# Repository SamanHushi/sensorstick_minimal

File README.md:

# minimal-co2-pcb

> [!NOTE]
> This board has not been physically tested.

## Todo

- [ ] Integrate into case

## Build of Materials (BOM)

Interactive BOM: https://samanhushi.github.io/sensorstick_minimal/

- 1x [ESP32-C3 SuperMini](https://www.aliexpress.com/item/1005006599448997.html)
- 1x [USB A plug](https://www.lcsc.com/product-detail/usb-connectors_xkb-connection-u217-041n-4bv81_C319178.html/?href=jlc-SMT%2F%3Fhref%3Djlc-SMT)
- 1x [SCD40 CO2 sensor](https://de.aliexpress.com/item/1005002905505683.html)
- 1x [SGP40](https://www.mouser.de/ProductDetail/Sensirion/SGP40-D-R4?qs=yqaQSyyJnNgaRqiZfsbS1Q%3D%3D)
- 1x [SHT40](https://www.mouser.de/ProductDetail/Sensirion/SHT40-AD1B-R2?qs=zW32dvEIR3scTT6A4VuzaQ%3D%3D)
- 1x [Ambient Light Sensor](https://www.lcsc.com/product-detail/C504893.html?s_z=n_C504893)

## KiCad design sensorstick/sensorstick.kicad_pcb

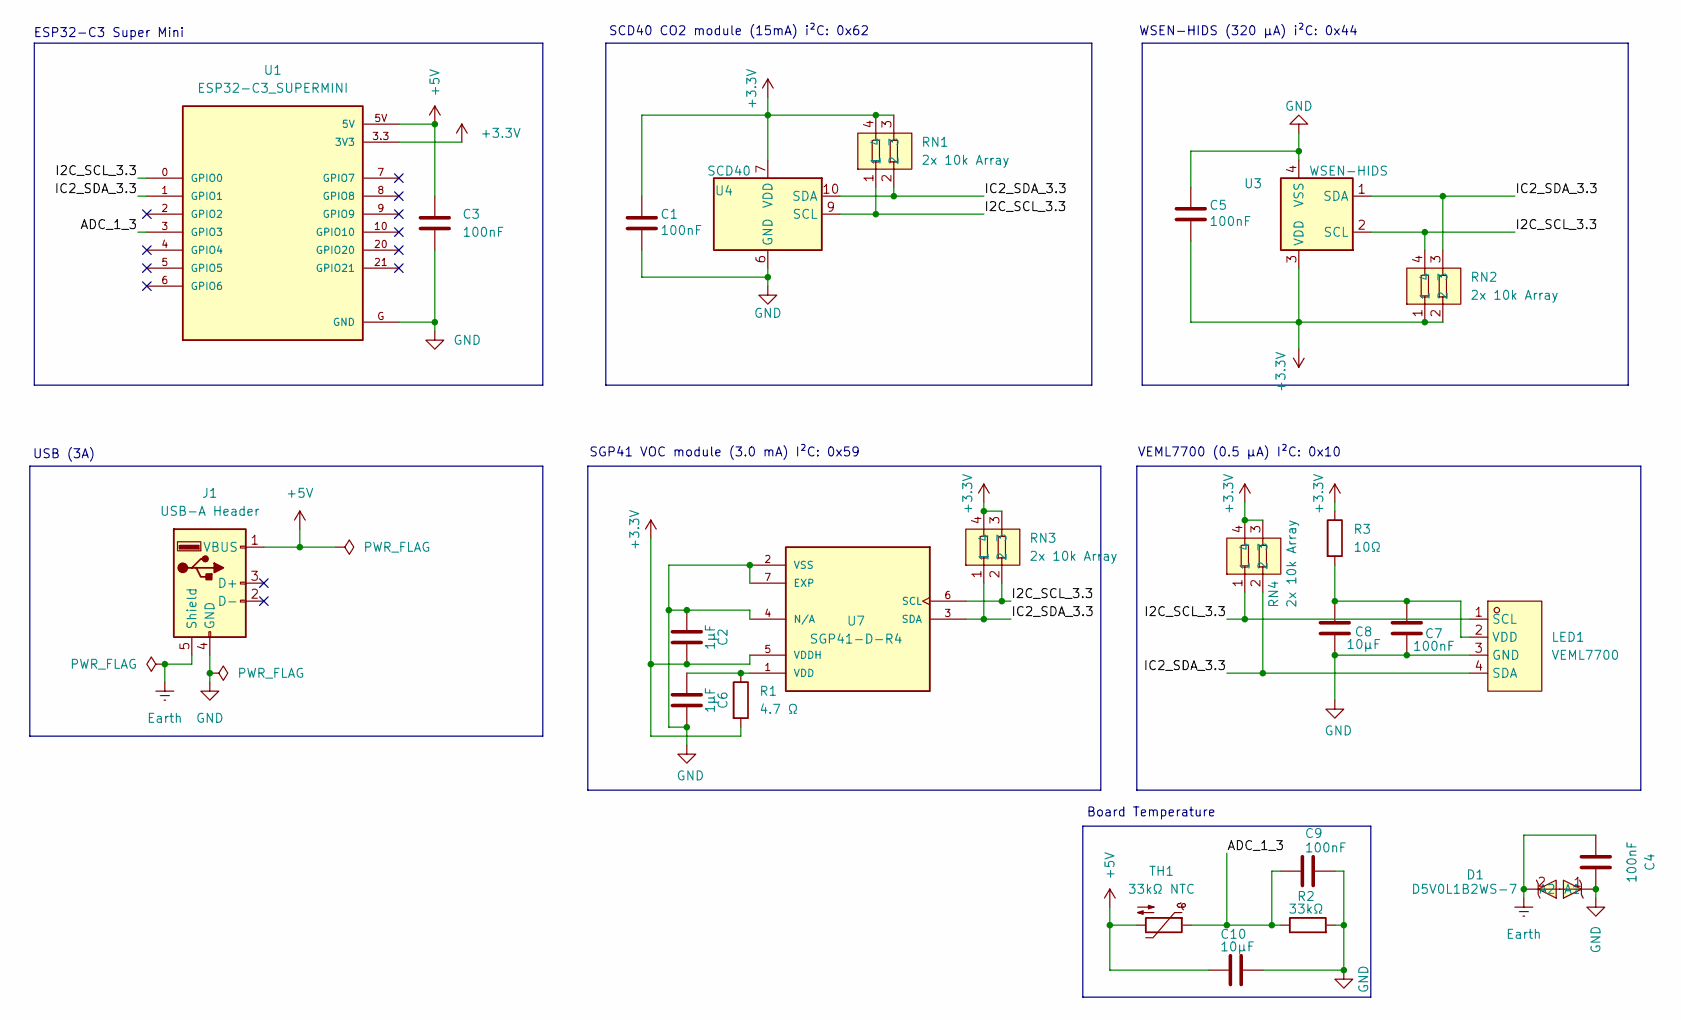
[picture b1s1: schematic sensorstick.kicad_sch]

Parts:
C1, C3, C4, C5, C7: 100nF; C_0603_1608Metric; partdb_id 573; LCSC C1591
C2, C6: 1μF; C_0603_1608Metric; partdb_id 428; LCSC C1591
C8: 10μF; C_0603_1608Metric; partdb_id 19; LCSC C1591
C9: 100nF; C_0603_1608Metric; partdb_id 573; LCSC C458914
C10: 10μF; C_0603_1608Metric; partdb_id 19; LCSC C458914
D1: D5V0L1B2WS-7; SOD-323_L1.8-W1.3-LS2.5-BI; partdb_id 429; LCSC Part C182013
J1: USB-A Header; USB-A-SMD_U217-041N-4BV81; partdb_id 248; LCSC Part C319178
LED1: VEML7700; LED-SMD_4P-L6.8-W2.4_VEML7700-TR; partdb_id 589; LCSC Part C504893
R1: 4.7 Ω; R_0603_1608Metric; partdb_id 330
R2: 33kΩ; R_0603_1608Metric; partdb_id 559
R3: 10Ω; R_0603_1608Metric; partdb_id 208
RN1, RN2, RN3, RN4: 2x 10k Array; RES-ARRAY-SMD_0402-4P-L1.0-W1.0-BL; partdb_id 431; LCSC Part C2765527
TH1: 33kΩ NTC; R_0603_1608Metric; partdb_id 571
U1: ESP32-C3_SUPERMINI; ESP32-C3_SUPERMINI_SMD; partdb_id 247
U3: WSEN-HIDS; Sensirion_DFN-4_1.5x1.5mm_P0.8mm_SHT4x_NoCentralPad; partdb_id 584
U4: SCD40; Sensirion_SCD4x-1EP_10.1x10.1mm_P1.25mm_EP4.8x4.8mm; partdb_id 566
U7: SGP41-D-R4; XDCR_SGP41-D-R4; PARTREV 1.0

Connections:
+3.3V: C1.2, C2.2, C5.1, R1.2, R3.1, RN1.3, RN1.4, RN2.1, RN2.2, RN3.3, RN3.4, RN4.3, RN4.4, U1.3.3 (3V3), U3.3 (VDD), U4.7 (VDD), U4.19 (VDD), U7.5 (VDDH)
+5V: C3.1, C10.1, J1.1 (VBUS), TH1.2, U1.5V
/ADC_1_3: C9.1, R2.1, TH1.1, U1.3 (GPIO3)
/I2C_SCL_3.3: LED1.1 (SCL), RN1.1, RN2.4, RN3.2, RN4.1, U1.0 (GPIO0), U3.2 (SCL), U4.9 (SCL), U7.6 (SCL)
/IC2_SDA_3.3: LED1.4 (SDA), RN1.2, RN2.3, RN3.1, RN4.2, U1.1 (GPIO1), U3.1 (SDA), U4.10 (SDA), U7.3 (SDA)
Earth: C4.1, D1.2 (A1), J1.5 (Shield), J1.6 (Shield)
GND: C1.1, C2.1, C3.2, C4.2, C5.2, C6.2, C7.2, C8.2, C9.2, C10.2, D1.1 (A2), J1.4 (GND), LED1.3 (GND), R2.2, U1.G (GND), U3.4 (VSS), U4.6 (GND), U4.20 (GND), U4.21 (GND), U7.2 (VSS), U7.4 (N/A), U7.7 (EXP)
unnamed: C7.1, C8.1, LED1.2 (VDD), R3.2
unnamed: C6.1, R1.1, U7.1 (VDD)

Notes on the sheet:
SCD40 CO2 module (15mA) i²C: 0x62
SGP41 VOC module (3.0 mA) I²C: 0x59
Board Temperature
ESP32-C3 Super Mini
WSEN-HIDS (320 μA) i²C: 0x44
USB (3A)
VEML7700 (0.5 μA) I²C: 0x10

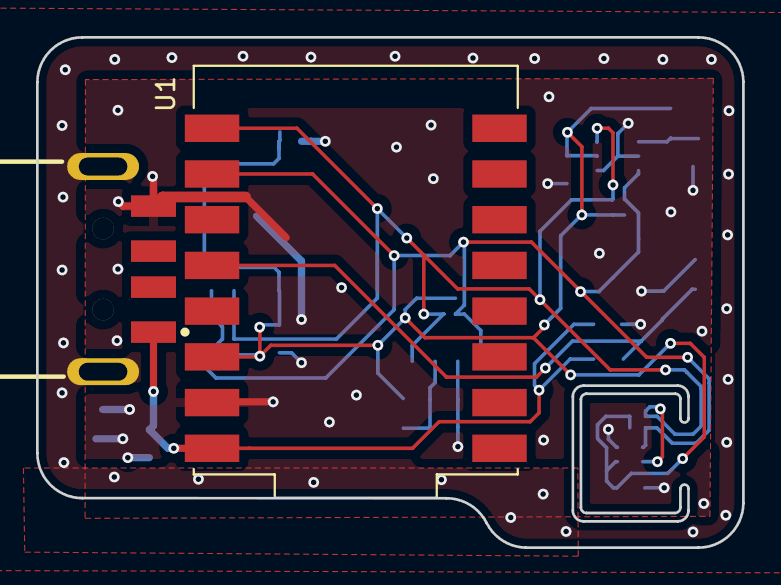
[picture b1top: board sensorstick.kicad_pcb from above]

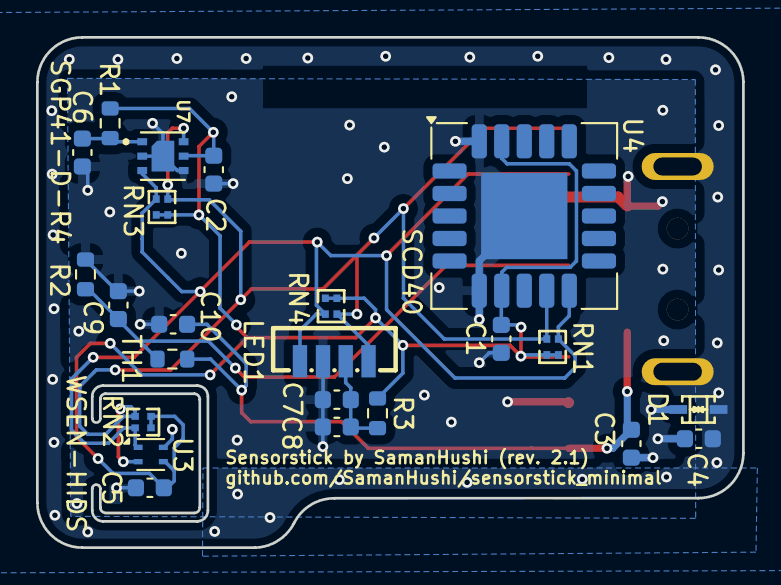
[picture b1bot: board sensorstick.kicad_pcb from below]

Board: 4 copper layers, 39.2 x 28.4 mm, 25 parts (23 on the bottom side), 9 nets.

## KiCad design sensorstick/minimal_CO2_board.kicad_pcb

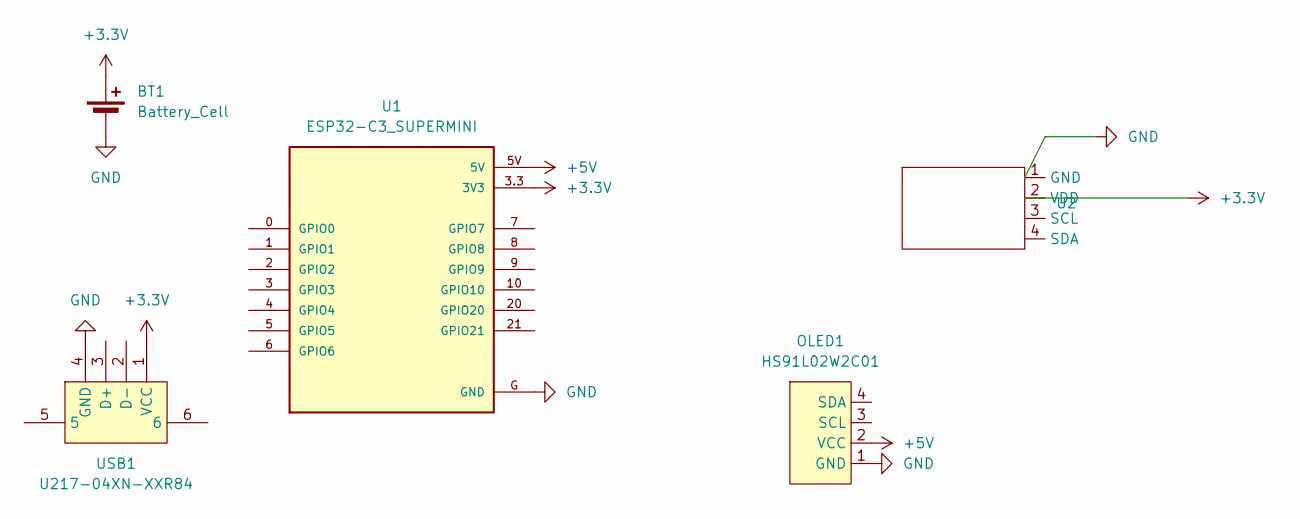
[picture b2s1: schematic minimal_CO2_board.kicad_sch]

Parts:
BT1: Battery_Cell; BatteryHolder_Keystone_1060_1x2032
OLED1: HS91L02W2C01; OLED-TH_L38.0-W12.0_HS91L02W2C01; LCSC Part C5248081
U1: ESP32-C3_SUPERMINI; ESP32-C3_SUPERMINI_SMD
U2: SCD40_CO2_module
USB1: U217-04XN-XXR84; USB-A-SMD_U217-041N-4BV81; LCSC Part C319178

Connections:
+3.3V: BT1.1 (+), U1.3.3 (3V3), U2.2 (VDD), USB1.1 (VCC)
+5V: OLED1.2 (VCC), U1.5V
GND: BT1.2 (-), OLED1.1 (GND), U1.G (GND), U2.1 (GND), USB1.4 (GND)

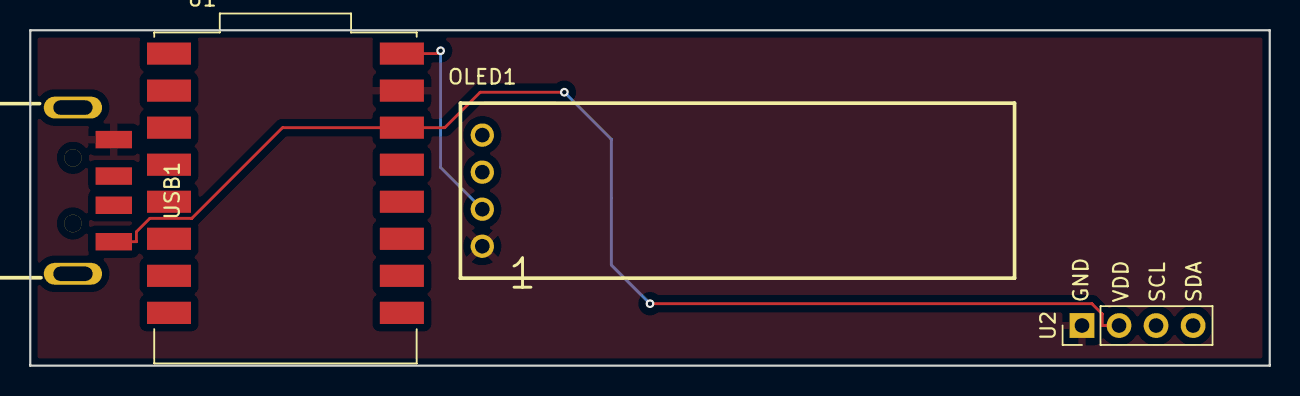
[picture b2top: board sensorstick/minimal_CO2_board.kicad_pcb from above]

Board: 2 copper layers, 85.0 x 23.0 mm, 5 parts (1 on the bottom side), 3 nets.

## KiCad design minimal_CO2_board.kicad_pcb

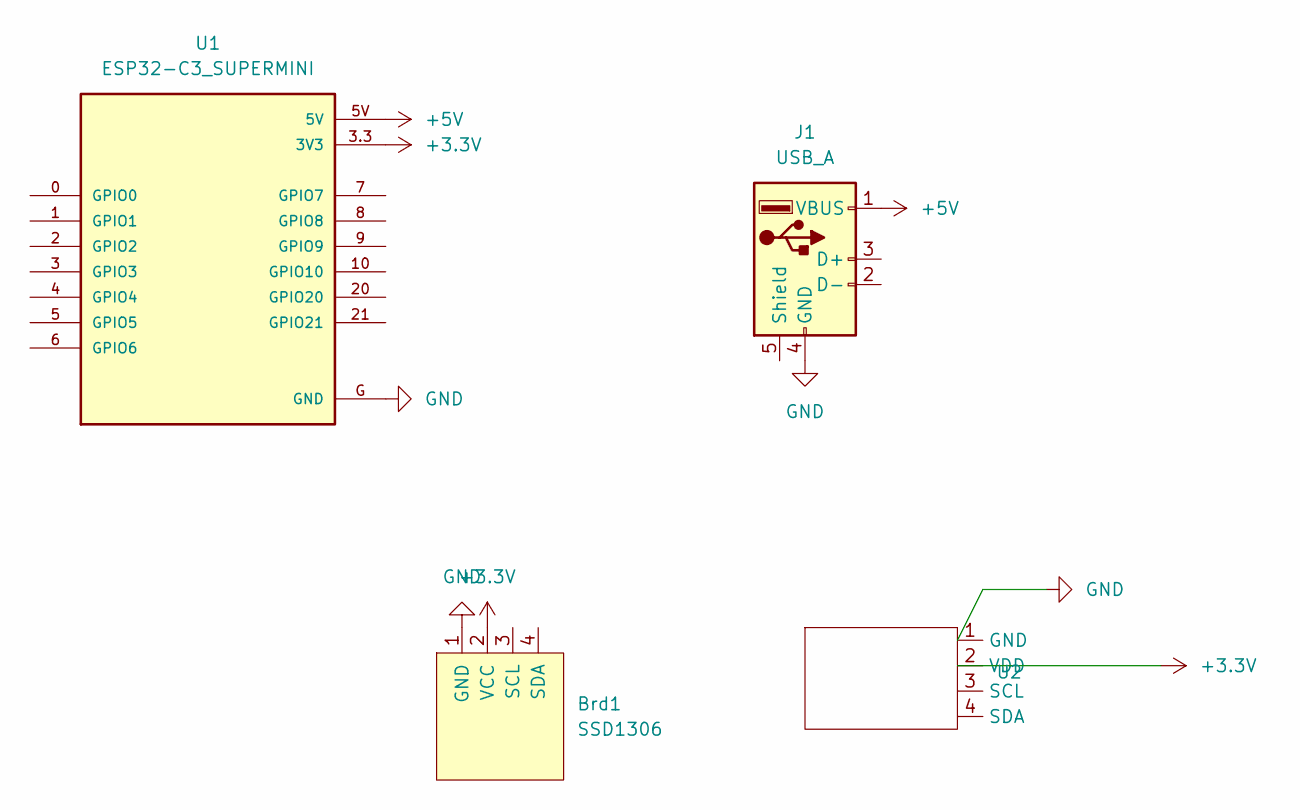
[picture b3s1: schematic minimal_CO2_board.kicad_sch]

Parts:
Brd1: SSD1306; 128x64OLED
J1: USB_A; USB_A_CNCTech_1001-011-01101_Horizontal
U1: ESP32-C3_SUPERMINI; ESP32-C3_SUPERMINI_SMD
U2: SCD40_CO2_module

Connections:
+3.3V: Brd1.2 (VCC), U1.3.3 (3V3), U2.2 (VDD)
+5V: J1.1 (VBUS), U1.5V
GND: Brd1.1 (GND), J1.4 (GND), U1.G (GND), U2.1 (GND)

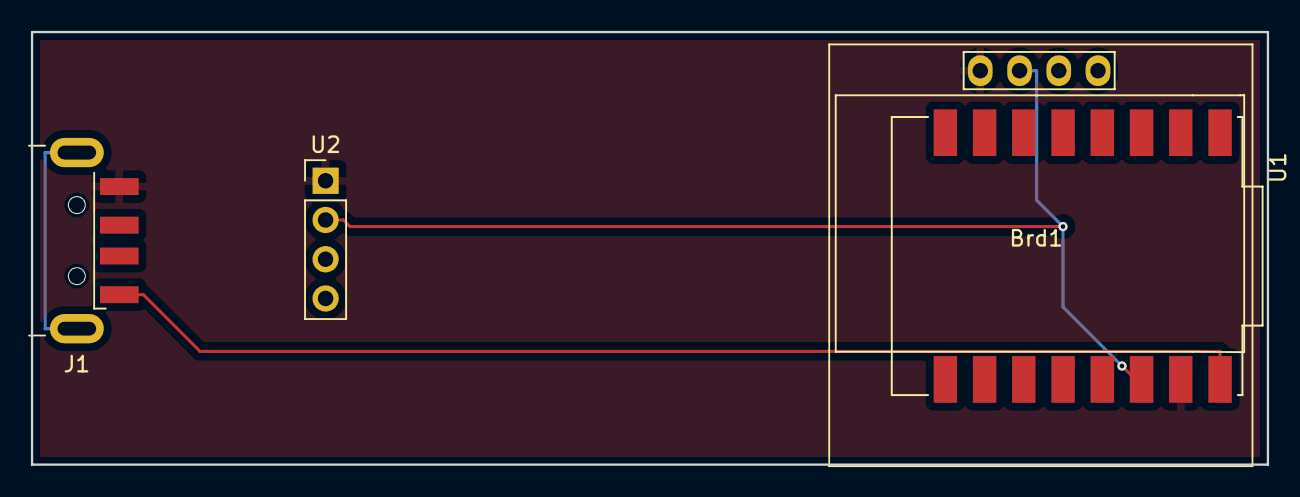
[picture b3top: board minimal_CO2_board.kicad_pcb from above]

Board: 2 copper layers, 80.0 x 28.0 mm, 4 parts (0 on the bottom side), 3 nets.

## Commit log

2025-02-27 init project
2025-02-28 add BOM in README
2025-02-28 move into sub folder
2025-02-28 add battery
2025-02-28 add stuff
2025-02-28 change location of models
2025-02-28 rename board
2025-02-28 fix pins
2025-03-01 add scd40 module
2025-03-11 progress
2025-03-12 add docs
2025-03-15 add condensator
2025-03-16 change filter
2025-03-16 updating routing
2025-03-16 GitHub action to build Pages
    add Makefile
    add help
    change URL
    move text
    add InteractiveHtmlBom
    test
2025-03-16 remove requirements.txt
2025-03-16 set LCSC #
2025-03-16 add LCSC & Description
2025-03-17 update filter
2025-03-17 Add standoff mounting holes to display footprint
2025-03-17 update footprints
2025-03-18 add 2 holes
2025-03-18 remove unused parts
2025-03-18 set value
2025-03-18 make base image more specific
2025-03-19 add kibot
2025-03-19 add loc
2025-03-19 rename job
2025-03-19 test
2025-03-19 extra_data_file
2025-03-19 simplify
2025-03-19 merge
2025-03-19 remove preflight
2025-03-19 hehe
2025-03-19 stuff
2025-03-19 config
2025-03-19 deploy
2025-03-19 add permission
2025-03-21 round edges
2025-03-22 add kibot to Makefile
2025-03-22 add JLCPCB output
2025-03-24 Bump actions/checkout from 2 to 4
    Bumps [actions/checkout](https://github.com/actions/checkout) from 2 to 4.
    - [Release notes](https://github.com/actions/checkout/releases)
    - [Changelog](https://github.com/actions/checkout/blob/main/CHANGELOG.md)
    - [Commits](https://github.com/actions/checkout/compare/v2...v4)
    ---
    updated-dependencies:
2025-03-27 sruff
2025-03-27 Marek did things
2025-03-27 move schematic arround & label name
2025-03-27 link LCSC parts
2025-03-27 add gerber files
2025-03-27 only deploy on main branch
2025-03-27 update org
2025-03-27 OLED: add front cortyard
2025-03-27 add cortyard
2025-03-27 move OLED
2025-04-18 cleanup LCSC part ID's
2025-04-27 release triggers file upload
2025-07-07 add GY-SGP30 symbol & footprint
2025-07-07 new sensor possition
2025-07-07 update gitignore
2025-07-07 added traceing
2025-07-07 changed esp possition
2025-10-13 minimal desin with new sensor
2025-10-14 finished first routing, open for review
2025-11-26 moved all parts on the backside for easyer asambly
2025-11-26 Update testing status in README
2025-11-26 added more vias
2025-11-28 added jcsc part numbers
2026-01-14 changed 3,3 to 1,8 module and i2c level shifter
2026-01-17 changed rev number to 2
2026-01-23 added NTC for board Temperature and finaly touch bevore ordering the PCB
2026-01-23 changed ntc values
2026-01-27 changed sgp30 to sgp
2026-01-27 added VEML7700
    because of moving from SGP30 to SGP41 I got rid of everything handling 1.8V and 1.8V I²C with space on the pcb I now filled with a High Accuracy Ambient Light Sensor
2026-01-27 final touch for ordeing it
2026-02-26 Revise BOM with updated components and links
    Updated the Build of Materials (BOM) section with new components and corrected links.
2026-02-28 update workflow
2026-03-02 cleanup .gitignore
2026-03-02 build for jlcpcb including footprint values
2026-03-02 added partdb id to ci
2026-03-02 add partdb_id for part
2026-03-10 added partdb ids
2026-03-11 Update README with project details
    Add project description and note about testing status
2026-03-11 redo README
    Remove outdated project description and note.
